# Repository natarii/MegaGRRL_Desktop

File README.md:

# MegaGRRL Desktop
## Overview
**MegaGRRL Desktop** is a simplified, easier to assemble respin of the original MegaGRRL project. This is intended for those who wish to assemble their own with minimal surface mount soldering, or do not need portability.
## Assembly guide
[Click here for the assembly guide.](https://git.agiri.ninja/natalie/MegaGRRL_Desktop/wikis/Assembly-guide) Bill of materials can be found [here](https://git.agiri.ninja/natalie/MegaGRRL_Desktop/wikis/BOM)
## Firmware flashing/changes
The portable and desktop MegaGRRL versions share a single codebase, contained in the [normal MegaGRRL repo](https://git.agiri.ninja/natalie/megagrrl). Before compiling, `main/hal.h` must be edited to specify that the desktop version is built. More details on this are available in the MegaGRRL project repo's readme.

A simplified flashing guide is available for Windows users [here](https://git.agiri.ninja/snippets/3).
## PCB manufacturing considerations
The board is a fairly standard 2-layer board. Please ensure that your PCB manufacturer handles the plated slots on the headphone jack correctly. The DRC rules are set for tented vias - these are preferable for aesthetics, but are otherwise not required. Please note if exporting your own gerbers that the art for the top and bottom of the PCB are on layers 200 (top) and 201 (bottom). Pre-exported gerbers for JLCPCB can be found in the `gerbers/` directory.
## 3D Printing
`mgd_base.stl` is an STL file for a 3D-printable baseplate for the MegaGRRL Desktop board. This provides a nice flat bottom surface and also supports the PCB underneath areas that undergo flexing (buttons, IC sockets). The original OpenSCAD source file is also available. 100% infill is recommended, and printing with a brim may help bed adhesion. Supports are needed due to the recessed screw holes. **The STL and SCAD files have recently been updated to be sized in mm instead of mil.** Previously they required scaling before printing, but this should no longer be required. If you are using a paid 3D printing service, please double-check the size before ordering!
## License
The schematic, PCB, and baseplate are licensed under CERN-OHL-S v2.
## Beware Fake Chips!

[WIP guide on detecting fake chips](https://git.agiri.ninja/natalie/MegaGRRL_Desktop/-/wikis/Identifying-fake-YM2612s)

Many of the YM2612s being sold on eBay are fake. Chips are very often remarked to make them appear new, and that has been ongoing for a long time, but recently myself and friends have received completely fake, non-working chips from multiple eBay sellers. If you are unsure about chips you received, email me a photo and I'll check them out. Also, I have had much better luck receiving legit YM3438s from eBay, so that may be the way to go. I recommend YM3438 anyway due to its improved sound quality.

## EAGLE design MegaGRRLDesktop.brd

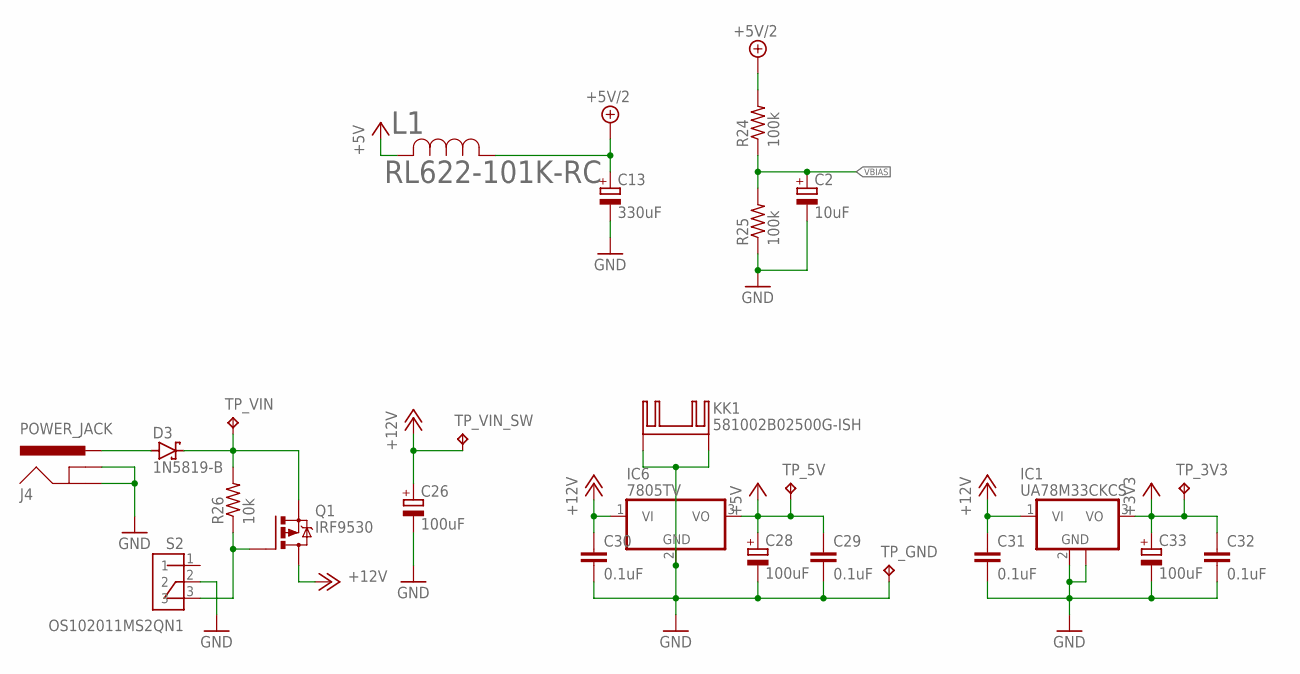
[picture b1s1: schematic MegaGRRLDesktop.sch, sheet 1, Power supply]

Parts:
C2: 10uF; E2,5-5
C13: 330uF; E2,5-7
C26, C28, C33: 100uF; E2,5-7
C29, C30, C31, C32: 0.1uF; C025-024X044
D3: 1N5819-B; DO41-7.6
IC1: UA78M33CKCS; TO220H
IC6: 7805TV; TO220V
J4: POWER_JACK; POWER_JACK_PTH
KK1: 581002B02500G-ISH
L1: RL622-101K-RC; RL622_SERIES
Q1: IRF9530; TO220BV
R24, R25: 100k; 0204/7
R26: 10k; 0204/7
S2: OS102011MS2QN1; SW_OS102011MS2QN1
TP_3V3, TP_5V: TPB1,27; B1,27
TP_GND: TPB1,27; B1,27
TP_VIN: TPB1,27; B1,27
TP_VIN_SW: TPB1,27; B1,27

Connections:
+3V3: C32.1, C33.+, IC1.3 (VO), TP_3V3.TP; also elsewhere on the board
+5V: C28.+, C29.1, IC6.3 (VO), L1.2, TP_5V.TP; also elsewhere on the board
+5V/2: C13.+, L1.1, R24.2; also elsewhere on the board
+12V: C26.+, C30.1, C31.1, IC1.1 (VI), IC6.1 (VI), Q1.D, TP_VIN_SW.TP
GND: C2.-, C13.-, C26.-, C28.-, C29.2, C30.2, C31.2, C32.2, C33.-, IC1.2 (GND), IC1.TAB (GND), IC6.2 (GND), J4.GND, J4.GNDBREAK, KK1.B, KK1.B1, R25.1, S2.2, TP_GND.TP; also elsewhere on the board
unnamed: D3.C, Q1.S, R26.2, TP_VIN.TP
unnamed: Q1.G, R26.1, S2.3
unnamed: D3.A, J4.PWR
VBIAS: C2.+, R24.1, R25.2; also elsewhere on the board

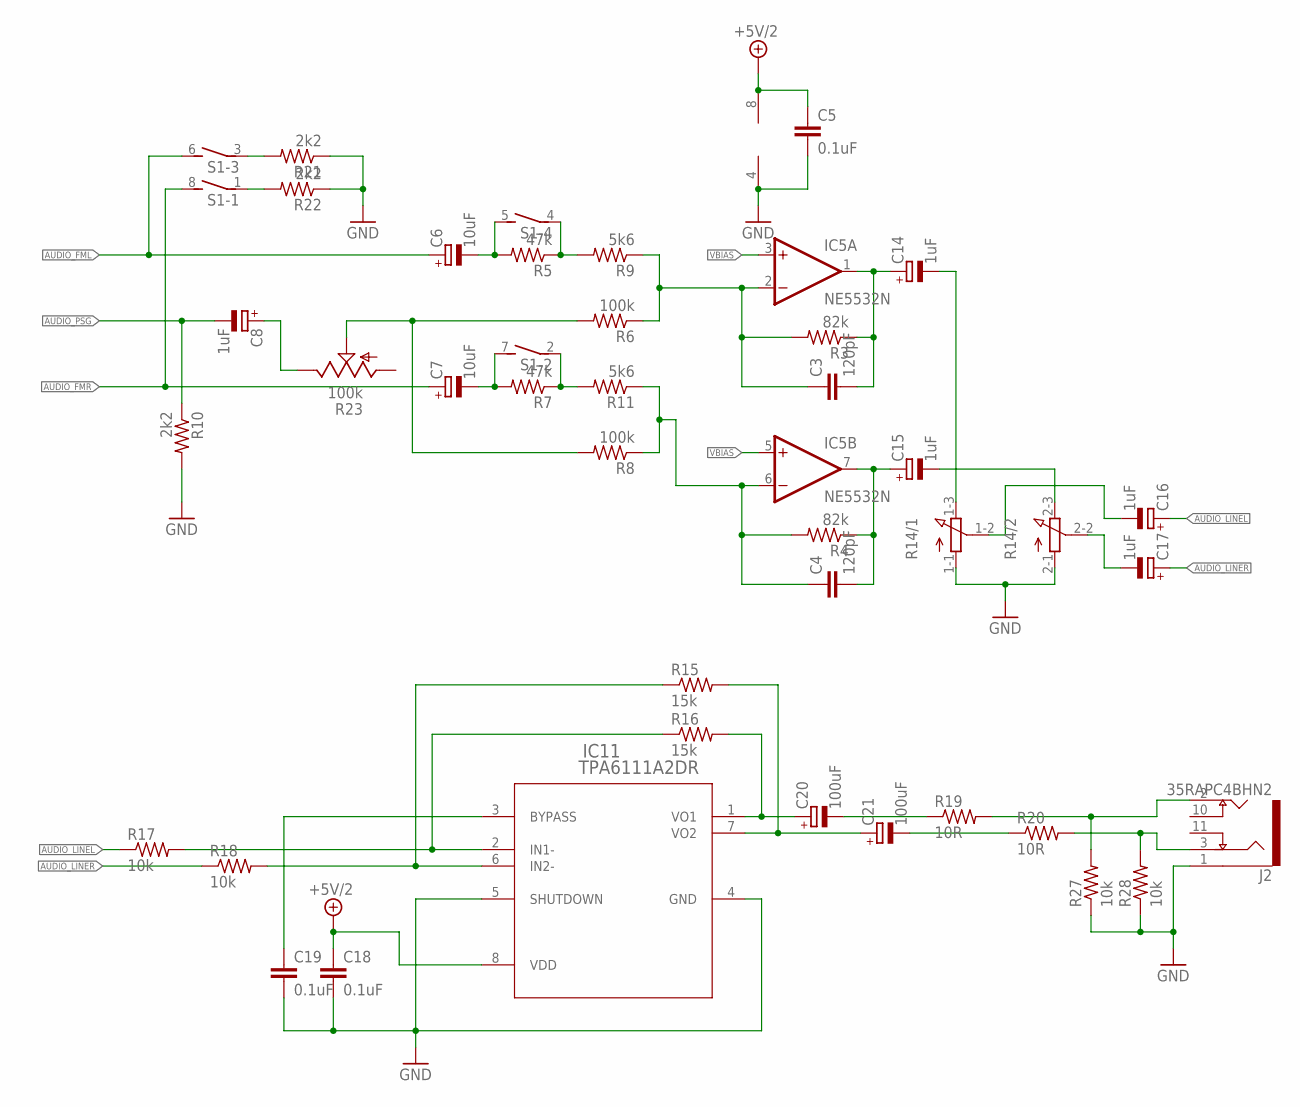
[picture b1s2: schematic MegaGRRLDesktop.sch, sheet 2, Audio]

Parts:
C3, C4: 120pF; C025-024X044
C5, C18, C19: 0.1uF; C025-024X044
C6, C7: 10uF; E2,5-5
C8, C14, C15, C16, C17: 1uF; E2-4
C20, C21: 100uF; E2,5-7
IC5: NE5532N; DIL08
IC11: TPA6111A2DR; D8
J2: 35RAPC4BHN2; SWITCHCRAFT_35RAPC4BHN2
R3, R4: 82k; 0204/7
R5, R7: 47k; 0204/7
R6, R8: 100k; 0204/7
R9, R11: 5k6; 0204/7
R10, R21, R22: 2k2; 0204/7
R14: 3RP/1610G
R15, R16: 15k; 0204/7
R17, R18, R27, R28: 10k; 0204/7
R19, R20: 10R; 0204/7
R23: 100k; S64W
S1: DIP04S

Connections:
+5V/2: C5.1, C18.1, IC5.8 (V+), IC11.8 (VDD); also elsewhere on the board
AUDIO_FML: C6.+, S1.6 (2); also elsewhere on the board
AUDIO_FMR: C7.+, S1.8 (2); also elsewhere on the board
AUDIO_LINEL: C16.+, R17.1
AUDIO_LINER: C17.+, R18.1
AUDIO_PSG: C8.-, R10.1; also elsewhere on the board
AUDIO_RAWL: C3.1, IC5.2 (-IN), R3.2, R6.1, R9.1
AUDIO_RAWR: C4.1, IC5.6 (-IN), R4.2, R8.1, R11.1
GND: C5.2, C18.2, C19.2, IC5.4 (V-), IC11.4 (GND), IC11.5 (SHUTDOWN), J2.1 (SLEEVE), R10.2, R14.1-1 (A), R14.2-1 (A), R21.1, R22.1, R27.1, R28.1; also elsewhere on the board
unnamed: R7.1, R11.2, S1.2 (1)
unnamed: C3.2, C14.+, IC5.1 (OUT), R3.1
unnamed: C4.2, C15.+, IC5.7 (OUT), R4.1
unnamed: C14.-, R14.1-3 (E)
unnamed: R6.2, R8.2, R23.S
unnamed: C7.-, R7.2, S1.7 (2)
unnamed: C6.-, R5.2, S1.5 (2)
unnamed: C15.-, R14.2-3 (E)
unnamed: C16.-, R14.1-2 (S)
unnamed: C17.-, R14.2-2 (S)
unnamed: IC11.2 (IN1-), R16.1, R17.2
unnamed: IC11.6 (IN2-), R15.1, R18.2
unnamed: C20.+, IC11.1 (VO1), R16.2
unnamed: C21.+, IC11.7 (VO2), R15.2
unnamed: C19.1, IC11.3 (BYPASS)
unnamed: J2.2 (TIP), R19.2, R27.2
unnamed: C20.-, R19.1
unnamed: C21.-, R20.1
unnamed: J2.3 (RING), R20.2, R28.2
unnamed: R5.1, R9.2, S1.4 (1)
unnamed: R21.2, S1.3 (1)
unnamed: R22.2, S1.1
unnamed: C8.+, R23.E
VBIAS: IC5.3 (+IN), IC5.5 (+IN); also elsewhere on the board

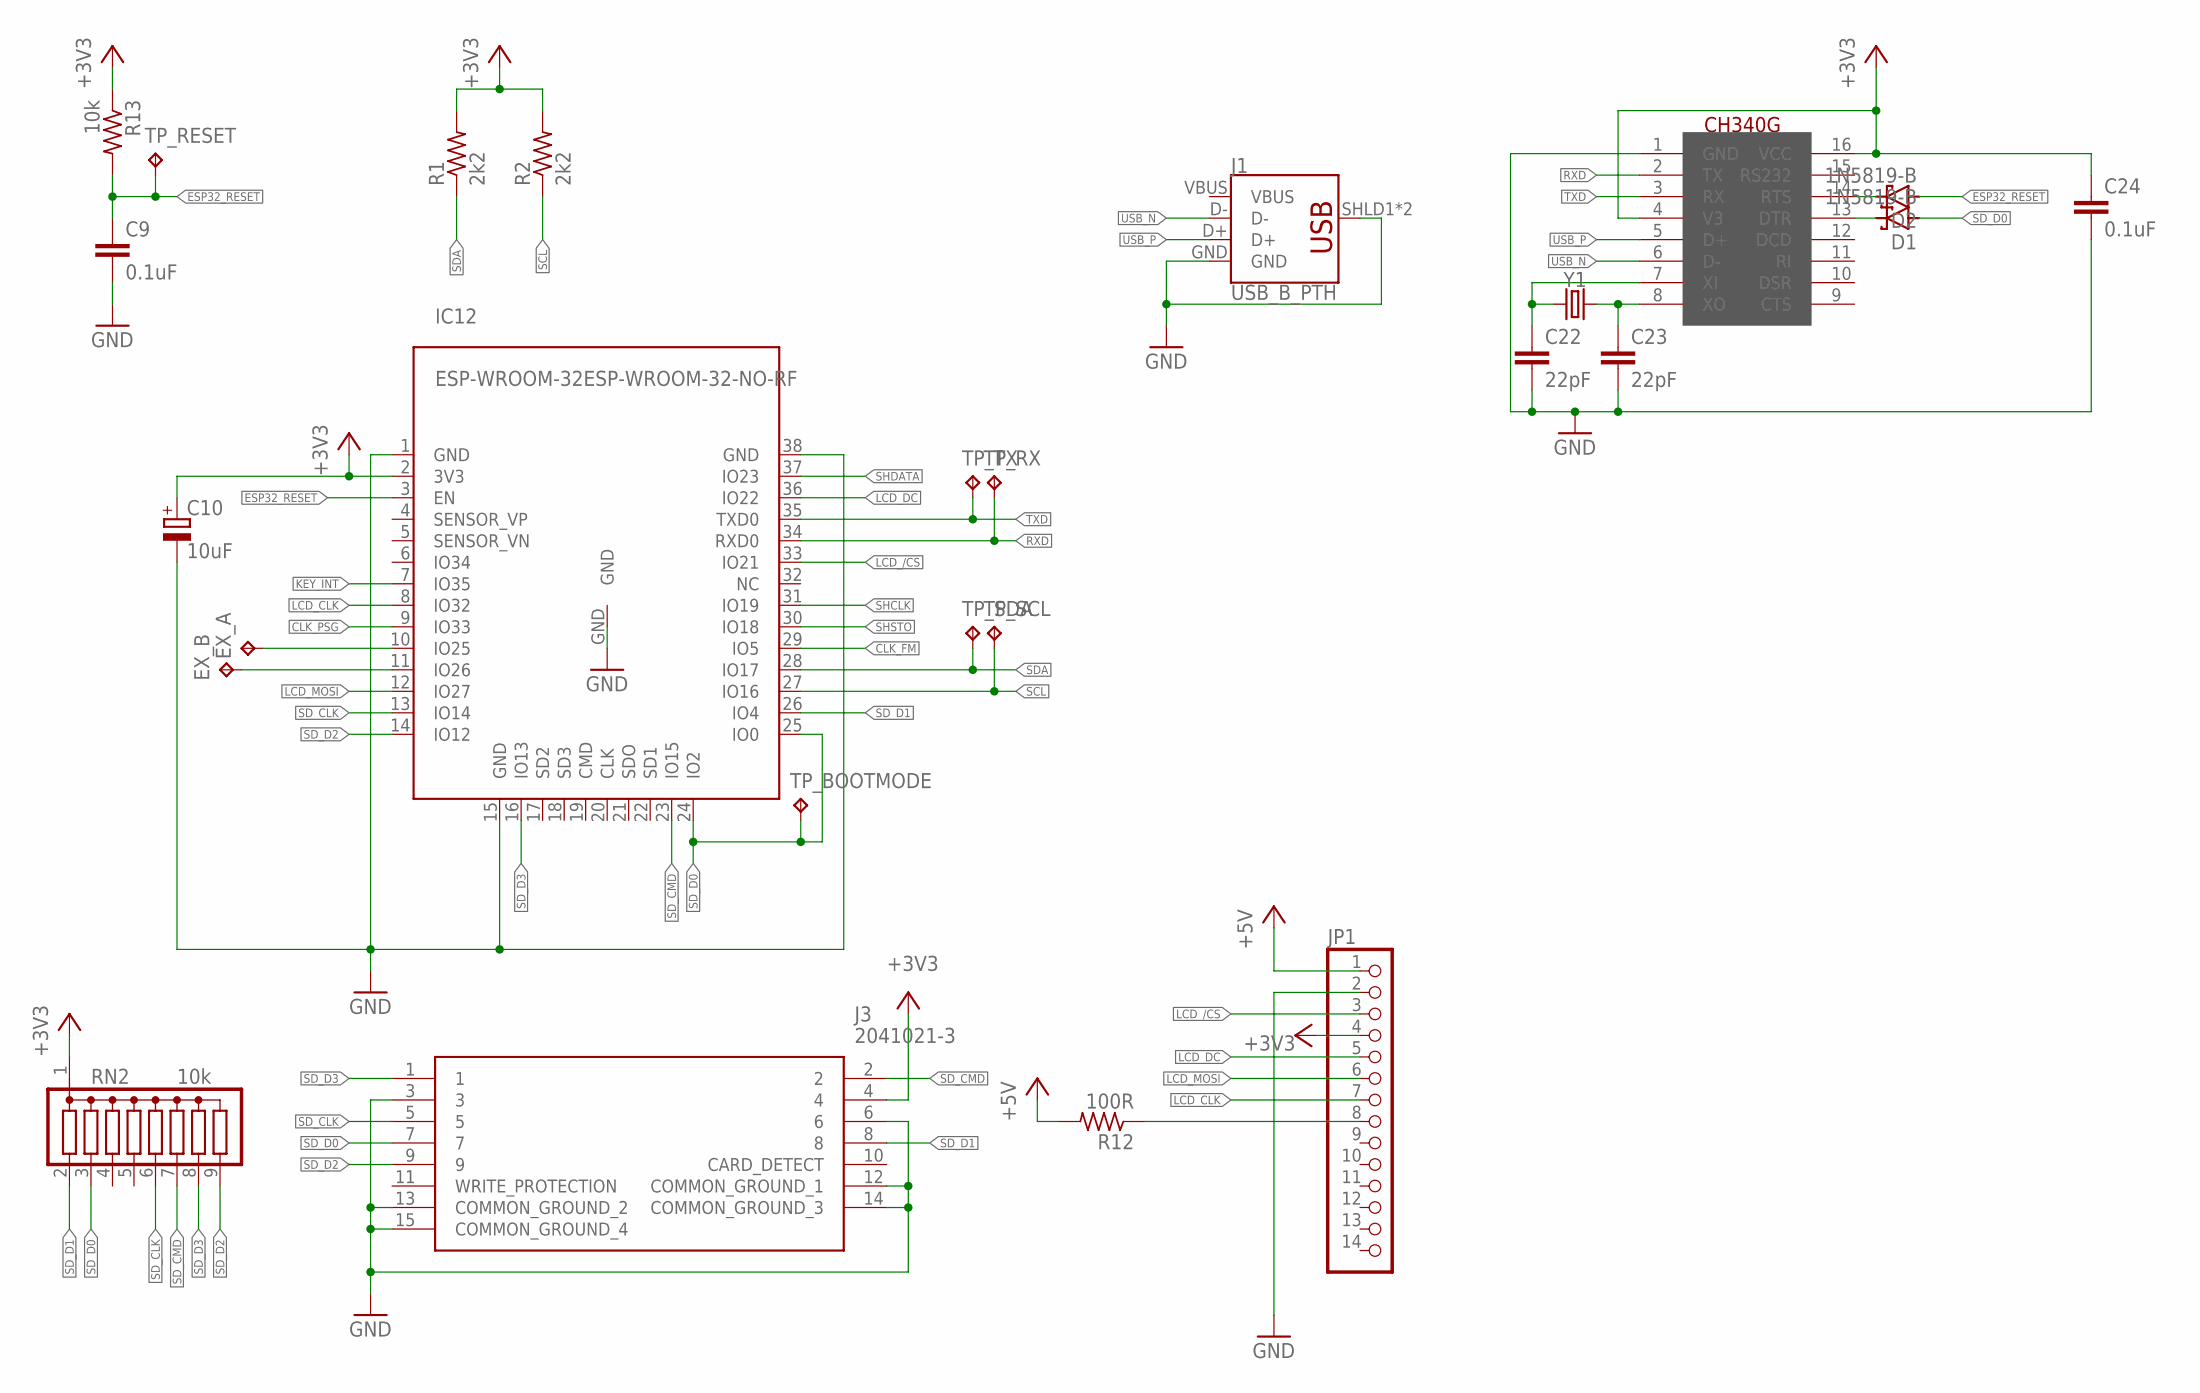
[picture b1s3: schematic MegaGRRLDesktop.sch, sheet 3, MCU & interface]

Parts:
C9, C24: 0.1uF; C025-024X044
C10: 10uF; E2,5-5
C22, C23: 22pF; C025-024X044
D1, D2: 1N5819-B; DO41-7.6
EX_A: TPB1,27; B1,27
EX_B: TPB1,27; B1,27
IC12: ESP-WROOM-32ESP-WROOM-32-NO-RF; ESP-WROOM-32-NO-RF
IC14: CH340G; SOIC16
J1: USB_B_PTH; USB-B-PTH
J3: 2041021-3; 2041021-3_2
JP1: ILI9341_2_4
R1, R2: 2k2; 0204/7
R12: 100R; 0204/7
R13: 10k; 0204/7
RN2: 10k; SIL9
TP_BOOTMODE: TPB1,27; B1,27
TP_RESET: TPB1,27; B1,27
TP_RX: TPB1,27; B1,27
TP_SCL: TPB1,27; B1,27
TP_SDA: TPB1,27; B1,27
TP_TX: TPB1,27; B1,27
Y1: CRYSTALPTH-HC49US; HC49US

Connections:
+3V3: C10.+, C24.1, IC12.2 (3V3), IC14.4 (V3), IC14.16 (VCC), J3.4, JP1.4, R1.2, R2.2, R13.1, RN2.1; also elsewhere on the board
+5V: JP1.1, R12.2; also elsewhere on the board
CLK_FM: IC12.29 (IO5); also elsewhere on the board
CLK_PSG: IC12.9 (IO33); also elsewhere on the board
ESP32_RESET: C9.1, D2.A, IC12.3 (EN), R13.2, TP_RESET.TP
GND: C9.2, C10.-, C22.2, C23.2, C24.2, IC12.1 (GND), IC12.15 (GND), IC12.38 (GND), IC12.GND, IC14.1 (GND), J1.GND, J1.SHLD1 (SHIELD), J1.SHLD2 (SHIELD), J3.3, J3.6, J3.12 (COMMON_GROUND_1), J3.13 (COMMON_GROUND_2), J3.14 (COMMON_GROUND_3), J3.15 (COMMON_GROUND_4), JP1.2; also elsewhere on the board
KEY_INT: IC12.7 (IO35); also elsewhere on the board
LCD_/CS: IC12.33 (IO21), JP1.3
LCD_CLK: IC12.8 (IO32), JP1.7
LCD_DC: IC12.36 (IO22), JP1.5
LCD_MOSI: IC12.12 (IO27), JP1.6
unnamed: C23.1, IC14.8 (XO), Y1.2
unnamed: C22.1, IC14.7 (XI), Y1.1
unnamed: JP1.8, R12.1
unnamed: D1.C, IC14.13 (DTR)
unnamed: D2.C, IC14.14 (RTS)
unnamed: EX_A.TP, IC12.10 (IO25)
unnamed: EX_B.TP, IC12.11 (IO26)
RXD: IC12.34 (RXD0), IC14.2 (TX), TP_RX.TP
SCL: IC12.27 (IO16), R2.1, TP_SCL.TP; also elsewhere on the board
SDA: IC12.28 (IO17), R1.1, TP_SDA.TP; also elsewhere on the board
SD_CLK: IC12.13 (IO14), J3.5, RN2.6
SD_CMD: IC12.23 (IO15), J3.2, RN2.7
SD_D0: D1.A, IC12.24 (IO2), IC12.25 (IO0), J3.7, RN2.3, TP_BOOTMODE.TP
SD_D1: IC12.26 (IO4), J3.8, RN2.2
SD_D2: IC12.14 (IO12), J3.9, RN2.9
SD_D3: IC12.16 (IO13), J3.1, RN2.8
SHCLK: IC12.31 (IO19); also elsewhere on the board
SHDATA: IC12.37 (IO23); also elsewhere on the board
SHSTO: IC12.30 (IO18); also elsewhere on the board
TXD: IC12.35 (TXD0), IC14.3 (RX), TP_TX.TP
USB_N: IC14.6 (D-), J1.D-
USB_P: IC14.5 (D+), J1.D+
VBUS: J1.VBUS

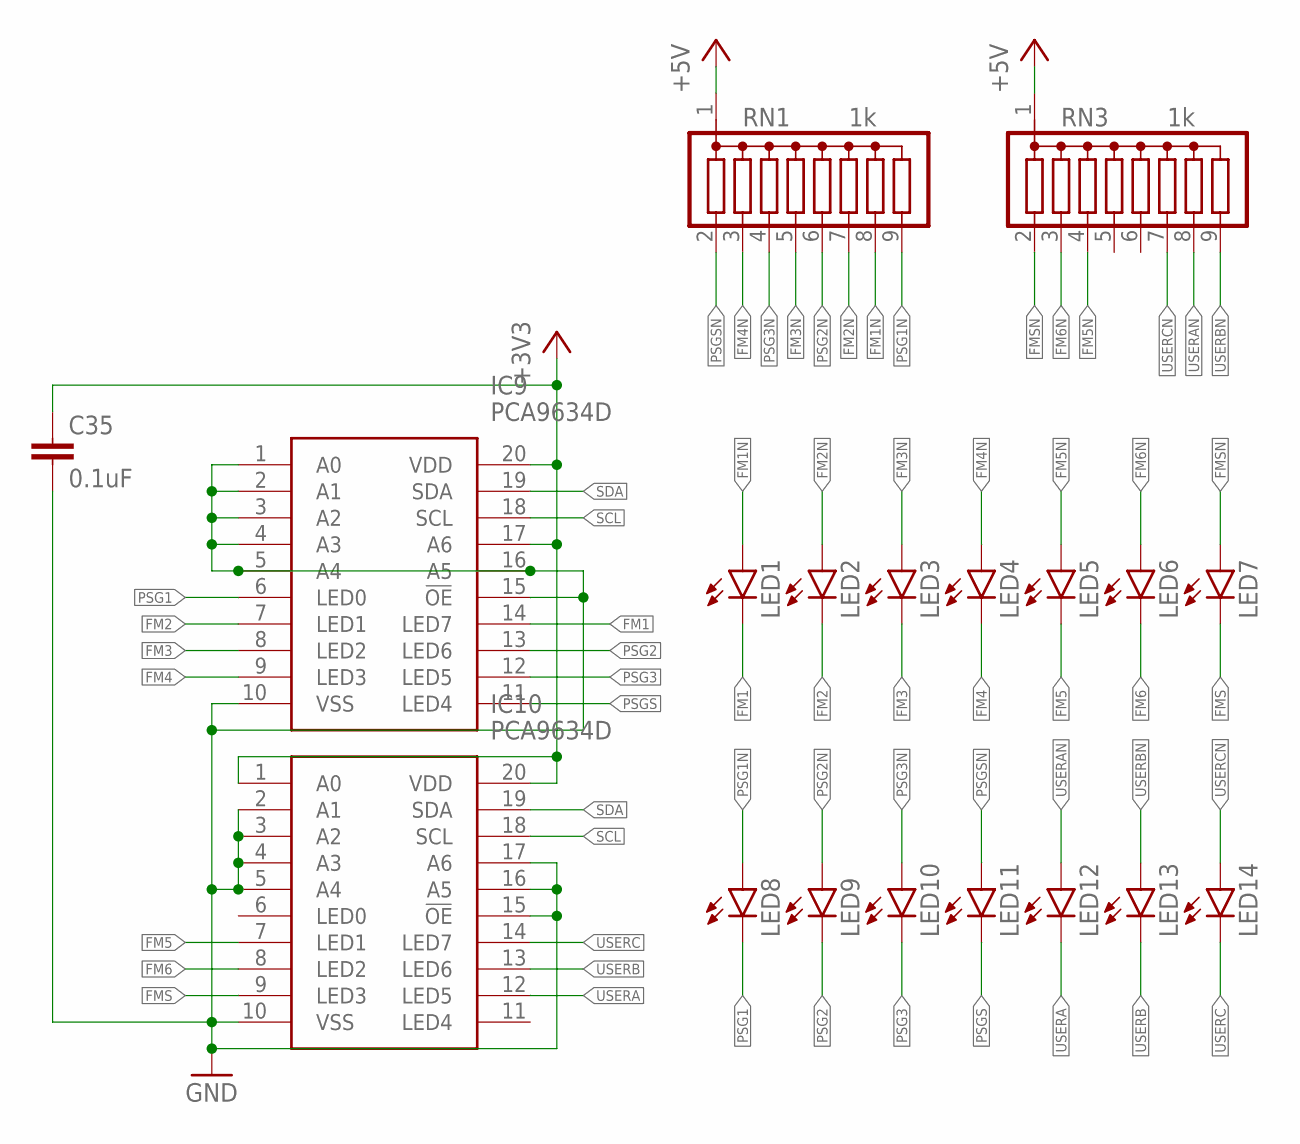
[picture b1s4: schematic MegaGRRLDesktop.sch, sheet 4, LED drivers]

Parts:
C35: 0.1uF; C025-024X044
IC9, IC10: PCA9634D; SOIC127P1032X265-20N
LED1, LED2, LED3, LED4, LED5, LED6, LED7, LED8, LED9, LED10, LED11, LED12, LED13, LED14: LED3MM
RN1, RN3: 1k; SIL9

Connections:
+3V3: C35.1, IC9.17 (A6), IC9.20 (VDD), IC10.1 (A0), IC10.20 (VDD); also elsewhere on the board
+5V: RN1.1, RN3.1; also elsewhere on the board
FM1: IC9.14 (LED7), LED1.K (C)
FM1N: LED1.A, RN1.8
FM2: IC9.7 (LED1), LED2.K (C)
FM2N: LED2.A, RN1.7
FM3: IC9.8 (LED2), LED3.K (C)
FM3N: LED3.A, RN1.5
FM4: IC9.9 (LED3), LED4.K (C)
FM4N: LED4.A, RN1.3
FM5: IC10.7 (LED1), LED5.K (C)
FM5N: LED5.A, RN3.4
FM6: IC10.8 (LED2), LED6.K (C)
FM6N: LED6.A, RN3.3
FMS: IC10.9 (LED3), LED7.K (C)
FMSN: LED7.A, RN3.2
GND: C35.2, IC9.1 (A0), IC9.2 (A1), IC9.3 (A2), IC9.4 (A3), IC9.5 (A4), IC9.10 (VSS), IC9.15 (!OE), IC9.16 (A5), IC10.2 (A1), IC10.3 (A2), IC10.4 (A3), IC10.5 (A4), IC10.10 (VSS), IC10.15 (!OE), IC10.16 (A5), IC10.17 (A6); also elsewhere on the board
PSG1: IC9.6 (LED0), LED8.K (C)
PSG1N: LED8.A, RN1.9
PSG2: IC9.13 (LED6), LED9.K (C)
PSG2N: LED9.A, RN1.6
PSG3: IC9.12 (LED5), LED10.K (C)
PSG3N: LED10.A, RN1.4
PSGS: IC9.11 (LED4), LED11.K (C)
PSGSN: LED11.A, RN1.2
SCL: IC9.18 (SCL), IC10.18 (SCL); also elsewhere on the board
SDA: IC9.19 (SDA), IC10.19 (SDA); also elsewhere on the board
USERA: IC10.12 (LED5), LED12.K (C)
USERAN: LED12.A, RN3.8
USERB: IC10.13 (LED6), LED13.K (C)
USERBN: LED13.A, RN3.9
USERC: IC10.14 (LED7), LED14.K (C)
USERCN: LED14.A, RN3.7

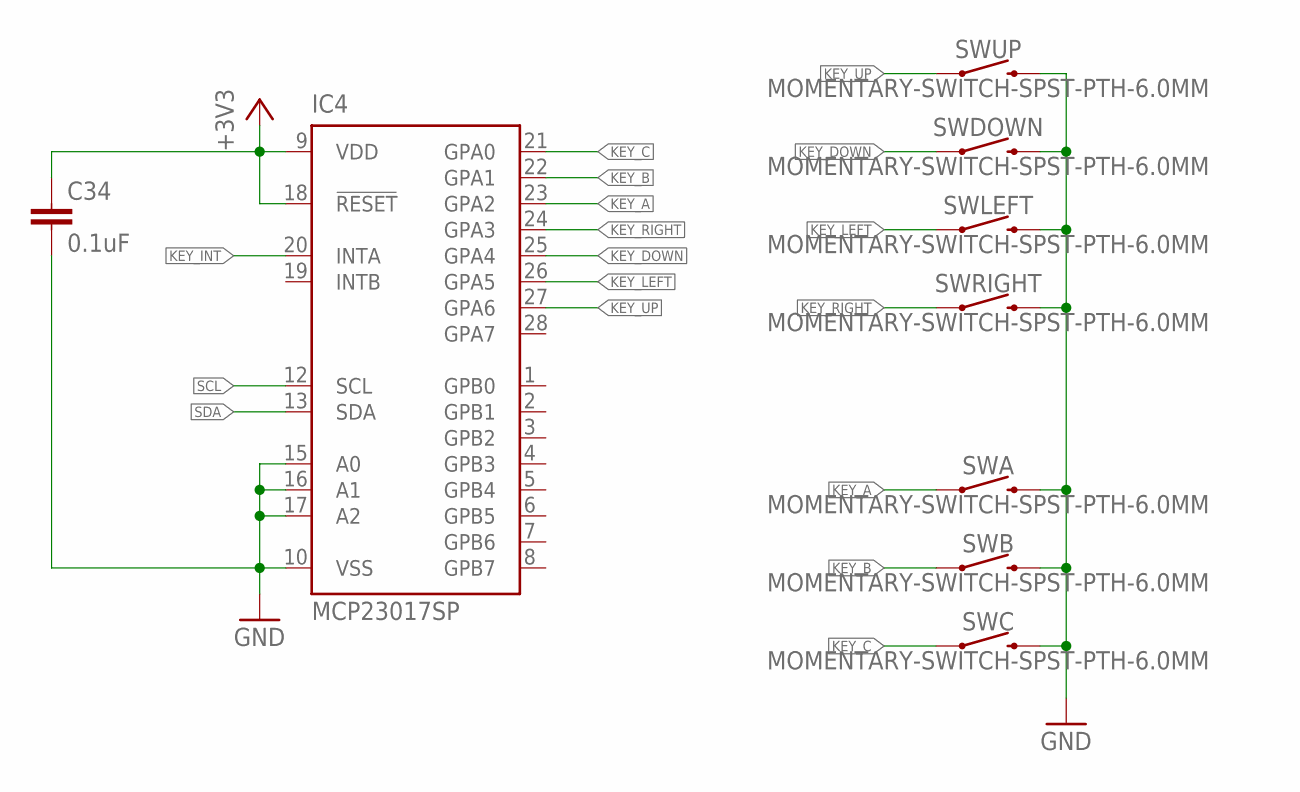
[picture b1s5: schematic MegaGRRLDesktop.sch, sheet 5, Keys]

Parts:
C34: 0.1uF; C025-024X044
IC4: MCP23017SP; DIL28-3
SWA: MOMENTARY-SWITCH-SPST-PTH-6.0MM; TACTILE_SWITCH_PTH_6.0MM
SWB: MOMENTARY-SWITCH-SPST-PTH-6.0MM; TACTILE_SWITCH_PTH_6.0MM
SWC: MOMENTARY-SWITCH-SPST-PTH-6.0MM; TACTILE_SWITCH_PTH_6.0MM
SWDOWN: MOMENTARY-SWITCH-SPST-PTH-6.0MM; TACTILE_SWITCH_PTH_6.0MM
SWLEFT: MOMENTARY-SWITCH-SPST-PTH-6.0MM; TACTILE_SWITCH_PTH_6.0MM
SWRIGHT: MOMENTARY-SWITCH-SPST-PTH-6.0MM; TACTILE_SWITCH_PTH_6.0MM
SWUP: MOMENTARY-SWITCH-SPST-PTH-6.0MM; TACTILE_SWITCH_PTH_6.0MM

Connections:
+3V3: C34.1, IC4.9 (VDD), IC4.18 (!RESET); also elsewhere on the board
GND: C34.2, IC4.10 (VSS), IC4.15 (A0), IC4.16 (A1), IC4.17 (A2), SWA.3 (2), SWB.3 (2), SWC.3 (2), SWDOWN.3 (2), SWLEFT.3 (2), SWRIGHT.3 (2), SWUP.3 (2); also elsewhere on the board
KEY_A: IC4.23 (GPA2), SWA.1
KEY_B: IC4.22 (GPA1), SWB.1
KEY_C: IC4.21 (GPA0), SWC.1
KEY_DOWN: IC4.25 (GPA4), SWDOWN.1
KEY_INT: IC4.20 (INTA); also elsewhere on the board
KEY_LEFT: IC4.26 (GPA5), SWLEFT.1
KEY_RIGHT: IC4.24 (GPA3), SWRIGHT.1
KEY_UP: IC4.27 (GPA6), SWUP.1
SCL: IC4.12 (SCL); also elsewhere on the board
SDA: IC4.13 (SDA); also elsewhere on the board

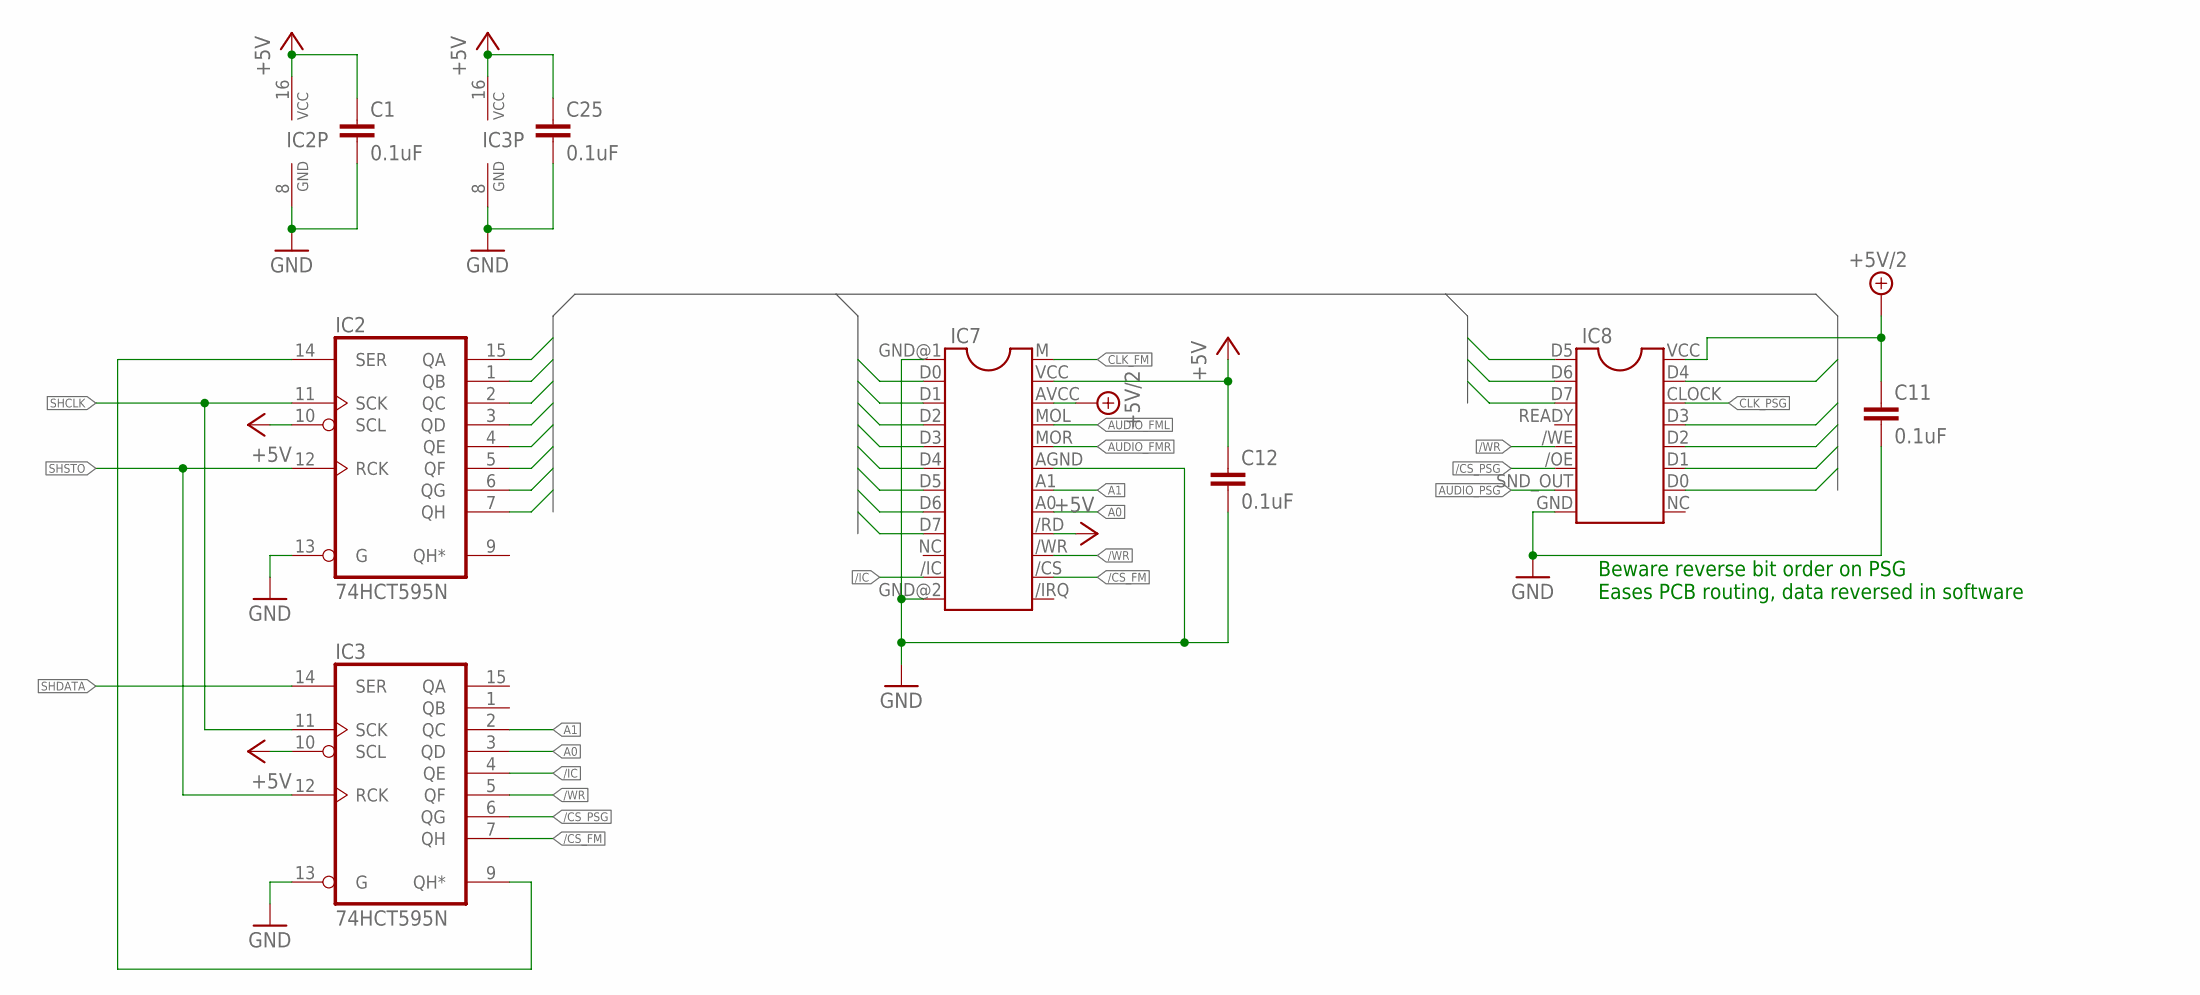
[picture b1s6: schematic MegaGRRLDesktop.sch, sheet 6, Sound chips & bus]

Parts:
C1, C11, C12, C25: 0.1uF; C025-024X044
IC2, IC3: 74HCT595N; DIL16
IC7: YM2612
IC8: SN76489

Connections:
+5V: C1.1, C12.1, C25.1, IC2.10 (SCL), IC2.16 (VCC), IC3.10 (SCL), IC3.16 (VCC), IC7./RD, IC7.VCC; also elsewhere on the board
+5V/2: C11.1, IC7.AVCC, IC8.VCC; also elsewhere on the board
/CS_FM: IC3.7 (QH), IC7./CS
/CS_PSG: IC3.6 (QG), IC8./OE
/IC: IC3.4 (QE), IC7./IC
/WR: IC3.5 (QF), IC7./WR, IC8./WE
A0: IC3.3 (QD), IC7.A0
A1: IC3.2 (QC), IC7.A1
AUDIO_FML: IC7.MOL; also elsewhere on the board
AUDIO_FMR: IC7.MOR; also elsewhere on the board
AUDIO_PSG: IC8.SND_OUT; also elsewhere on the board
CLK_FM: IC7.M; also elsewhere on the board
CLK_PSG: IC8.CLOCK; also elsewhere on the board
D0: IC2.15 (QA), IC7.D0, IC8.D7
D1: IC2.1 (QB), IC7.D1, IC8.D6
D2: IC2.2 (QC), IC7.D2, IC8.D5
D3: IC2.3 (QD), IC7.D3, IC8.D4
D4: IC2.4 (QE), IC7.D4, IC8.D3
D5: IC2.5 (QF), IC7.D5, IC8.D2
D6: IC2.6 (QG), IC7.D6, IC8.D1
D7: IC2.7 (QH), IC7.D7, IC8.D0
GND: C1.2, C11.2, C12.2, C25.2, IC2.8 (GND), IC2.13 (G), IC3.8 (GND), IC3.13 (G), IC7.AGND, IC7.GND@1 (GND), IC7.GND@2 (GND), IC8.GND; also elsewhere on the board
unnamed: IC2.14 (SER), IC3.9 (QH*)
SHCLK: IC2.11 (SCK), IC3.11 (SCK); also elsewhere on the board
SHDATA: IC3.14 (SER); also elsewhere on the board
SHSTO: IC2.12 (RCK), IC3.12 (RCK); also elsewhere on the board

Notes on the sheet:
Beware reverse bit order on PSG Eases PCB routing, data reversed in software

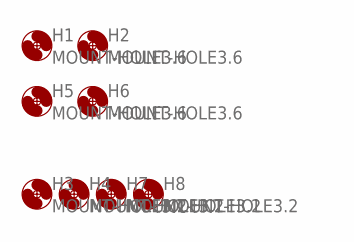
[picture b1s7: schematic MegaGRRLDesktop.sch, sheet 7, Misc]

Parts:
H1, H2, H5, H6: MOUNT-HOLE3.6; 3,6
H3, H4, H7, H8: MOUNT-HOLE3.2; 3,2

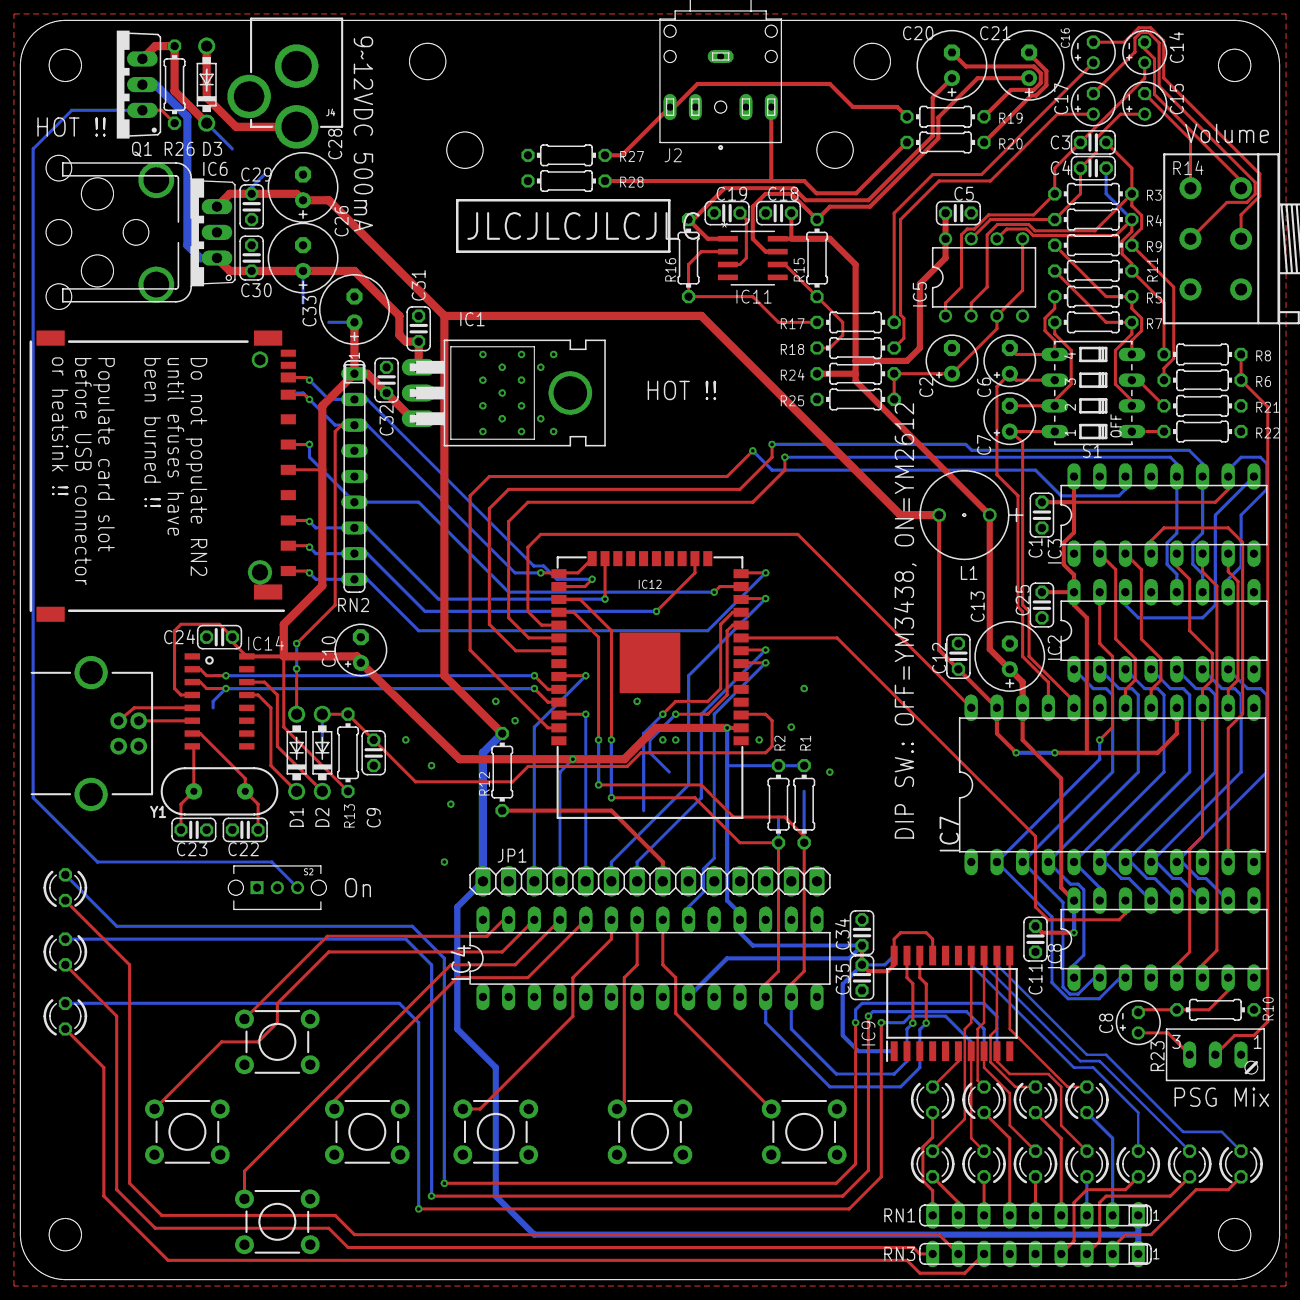
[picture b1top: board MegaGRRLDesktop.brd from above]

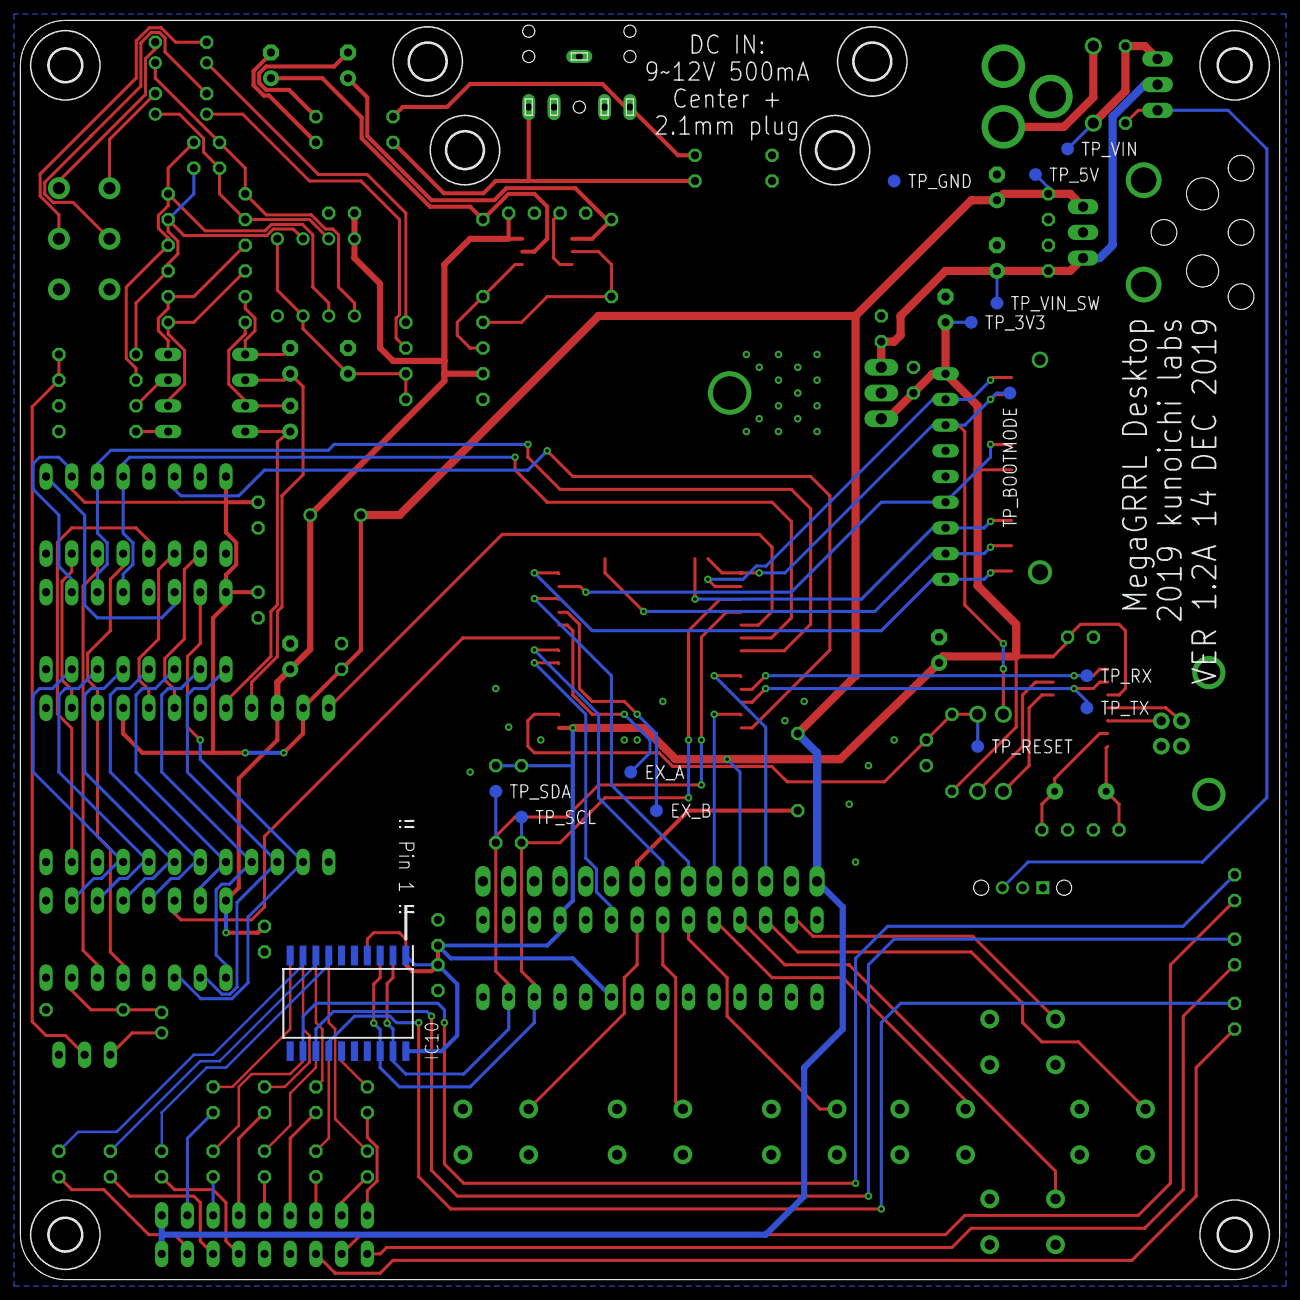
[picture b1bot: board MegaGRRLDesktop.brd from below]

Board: 2 copper layers, 124.5 x 124.5 mm, 134 parts (22 on the bottom side), 119 nets.

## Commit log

2019-09-08 add initial readme
2019-12-14 commit pcb
2019-12-15 add license
2019-12-22 fix 74HCT595
2019-12-22 commit schematic
2019-12-22 add premade gerbers
2019-12-22 add pcb image
2019-12-22 add schematic images
2019-12-24 add baseplate files
2020-01-11 add warning about fake YM2612s
2020-01-11 add link to fake chip examples
2020-02-05 commit STL files for baseplate
2020-02-05 add image of baseplate
2020-04-05 add note about art layers to readme
2020-04-05 rephrase parts of readme
2023-08-22 Bake in the mil to mm scaling for mgd_base
2024-04-09 Relicense to CERN-OHL-S v2

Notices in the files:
parts and their libraries:
SparkFun-Switches: Licensing: Creative Commons ShareAlike 4.0 International - https://creativecommons.org/licenses/by-sa/4.0
